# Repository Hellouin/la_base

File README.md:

# PROJET BASE RTK
## GPSE2026 - ENSICAEN
### Une base RTK permet de corriger des erreurs GPS

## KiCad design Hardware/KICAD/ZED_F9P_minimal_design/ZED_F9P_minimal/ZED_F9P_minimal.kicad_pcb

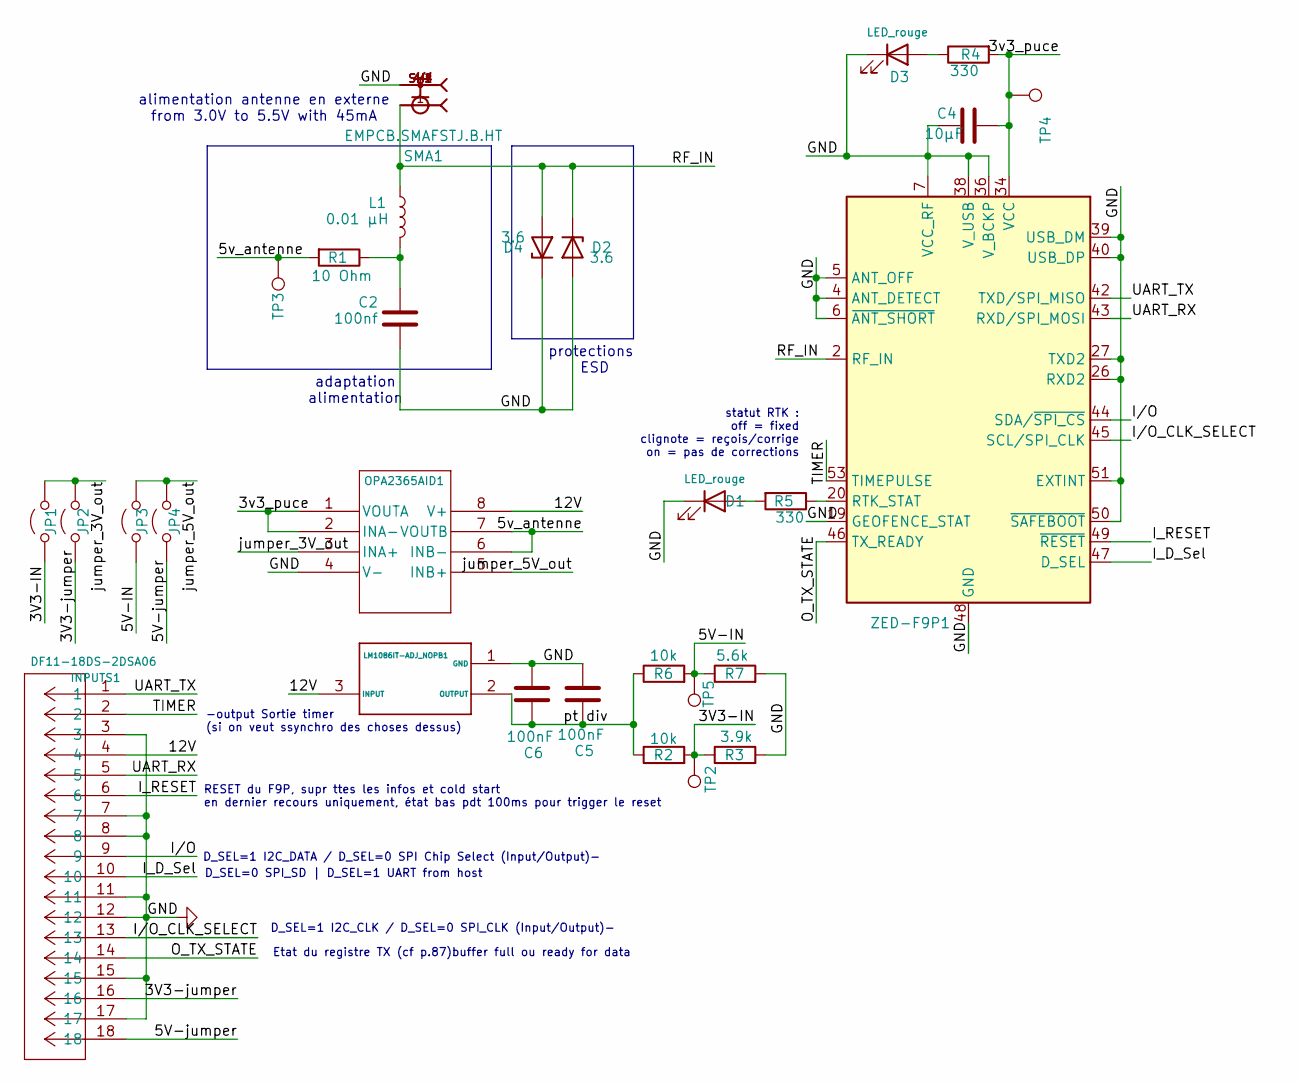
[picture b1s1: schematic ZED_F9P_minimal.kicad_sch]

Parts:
C2: 100nf; C_0805_2012Metric
C4: 10µF; C_0805_2012Metric
C5, C6: 100nF; C_0805_2012Metric
D1, D3: LED_rouge; LED_0805_2012Metric
D2, D4: 3.6; SOD323_DIO
INPUTS1: DF11-18DS-2DSA06; CON18_2X9_U_DF11_HIR
JP1, JP2, JP3, JP4: Jumper_2_Open; CON_1x02
L1: 0.01 µH; IND_786110A_WRE
LM1086IT-ADJ_NOPB1: NDE0003B
OPA2365AID1: D8
R1: 10 Ohm; RC0805N_YAG
R2, R6: 10k; YAG_R0805_YAG
R3: 3.9k; RC0805N_YAG
R4, R5: 330; RC0805N_YAG
R7: 5.6k; RC0805N_YAG
SMA1: EMPCB.SMAFSTJ.B.HT; TAOGLAS_EMPCB.SMAFSTJ.B.HT
TP2, TP3, TP4, TP5: TestPoint; CONN1_5011_KEY
ZED-F9P1: ZED-F9P; ublox_ZED

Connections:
/3V3-IN: JP1.1 (A), R2.2, R3.1, TP2.1
/3V3-jumper: INPUTS1.16, JP2.1 (A)
/3v3_puce: C4.1, OPA2365AID1.1 (VOUTA), OPA2365AID1.2 (INA-), R4.2, TP4.1, ZED-F9P1.33 (VCC), ZED-F9P1.34 (VCC)
/5V-IN: JP3.1 (A), R6.2, R7.1, TP5.1
/5V-jumper: INPUTS1.18, JP4.1 (A)
/5v_antenne: OPA2365AID1.6 (INB-), OPA2365AID1.7 (VOUTB), R1.2, TP3.1
/12V: INPUTS1.4, LM1086IT-ADJ_NOPB1.3 (INPUT), OPA2365AID1.8 (V+)
/I_D_Sel: INPUTS1.10, ZED-F9P1.47 (D_SEL)
/I_RESET: INPUTS1.6, ZED-F9P1.49 (~RESET)
/I/O: INPUTS1.9, ZED-F9P1.44 (SDA/~SPI_CS)
/I/O_CLK_SELECT: INPUTS1.13, ZED-F9P1.45 (SCL/SPI_CLK)
/O_TX_STATE: INPUTS1.14, ZED-F9P1.46 (TX_READY)
/RF_IN: D2.1 (K), D4.2 (A), L1.1, SMA1.1, ZED-F9P1.2 (RF_IN)
/TIMER: INPUTS1.2, ZED-F9P1.53 (TIMEPULSE)
/UART_RX: INPUTS1.5, ZED-F9P1.43 (RXD/SPI_MOSI)
/UART_TX: INPUTS1.1, ZED-F9P1.42 (TXD/SPI_MISO)
/jumper_3V_out: JP1.2 (B), JP2.2 (B), OPA2365AID1.3 (INA+)
/jumper_5V_out: JP3.2 (B), JP4.2 (B), OPA2365AID1.5 (INB+)
/pt div: C5.1, C6.1, LM1086IT-ADJ_NOPB1.2 (OUTPUT), R2.1, R6.1
GND: C2.2, C4.2, C5.2, C6.2, D1.1 (K), D2.2 (A), D3.1 (K), D4.1 (K), INPUTS1.3, INPUTS1.7, INPUTS1.8, INPUTS1.11, INPUTS1.12, INPUTS1.15, INPUTS1.17, LM1086IT-ADJ_NOPB1.1 (GND), OPA2365AID1.4 (V-), R3.2, R7.2, SMA1.SH1, SMA1.SH2, SMA1.SH3, SMA1.SH4, ZED-F9P1.1 (GND), ZED-F9P1.3 (GND), ZED-F9P1.4 (ANT_DETECT), ZED-F9P1.5 (ANT_OFF), ZED-F9P1.6 (~ANT_SHORT), ZED-F9P1.7 (VCC_RF), ZED-F9P1.12 (GND), ZED-F9P1.14 (GND), ZED-F9P1.19 (GEOFENCE_STAT), ZED-F9P1.26 (RXD2), ZED-F9P1.27 (TXD2), ZED-F9P1.32 (GND), ZED-F9P1.36 (V_BCKP), ZED-F9P1.37 (GND), ZED-F9P1.38 (V_USB), ZED-F9P1.39 (USB_DM), ZED-F9P1.40 (USB_DP), ZED-F9P1.41 (GND), ZED-F9P1.48 (GND), ZED-F9P1.50 (~SAFEBOOT), ZED-F9P1.51 (EXTINT), ZED-F9P1.55 (GND)
unnamed: C2.1, L1.2, R1.1
unnamed: D1.2 (A), R5.2
unnamed: D3.2 (A), R4.1
unnamed: R5.1, ZED-F9P1.20 (RTK_STAT)

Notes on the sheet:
alimentation antenne en externe from 3.0V to 5.5V with 45mA
RESET du F9P, supr ttes les infos et cold start en dernier recours uniquement, état bas pdt 100ms pour trigger le reset
D_SEL=1 I2C_DATA / D_SEL=0 SPI Chip Select (Input/Output)-
-output Sortie timer (si on veut ssynchro des choses dessus)
D_SEL=1 I2C_CLK / D_SEL=0 SPI_CLK (Input/Output)-
protections ESD
statut RTK : off = fixed clignote = reçois/corrige on = pas de corrections
Etat du registre TX (cf p.87)buffer full ou ready for data
D_SEL=0 SPI_SD | D_SEL=1 UART from host
adaptation alimentation

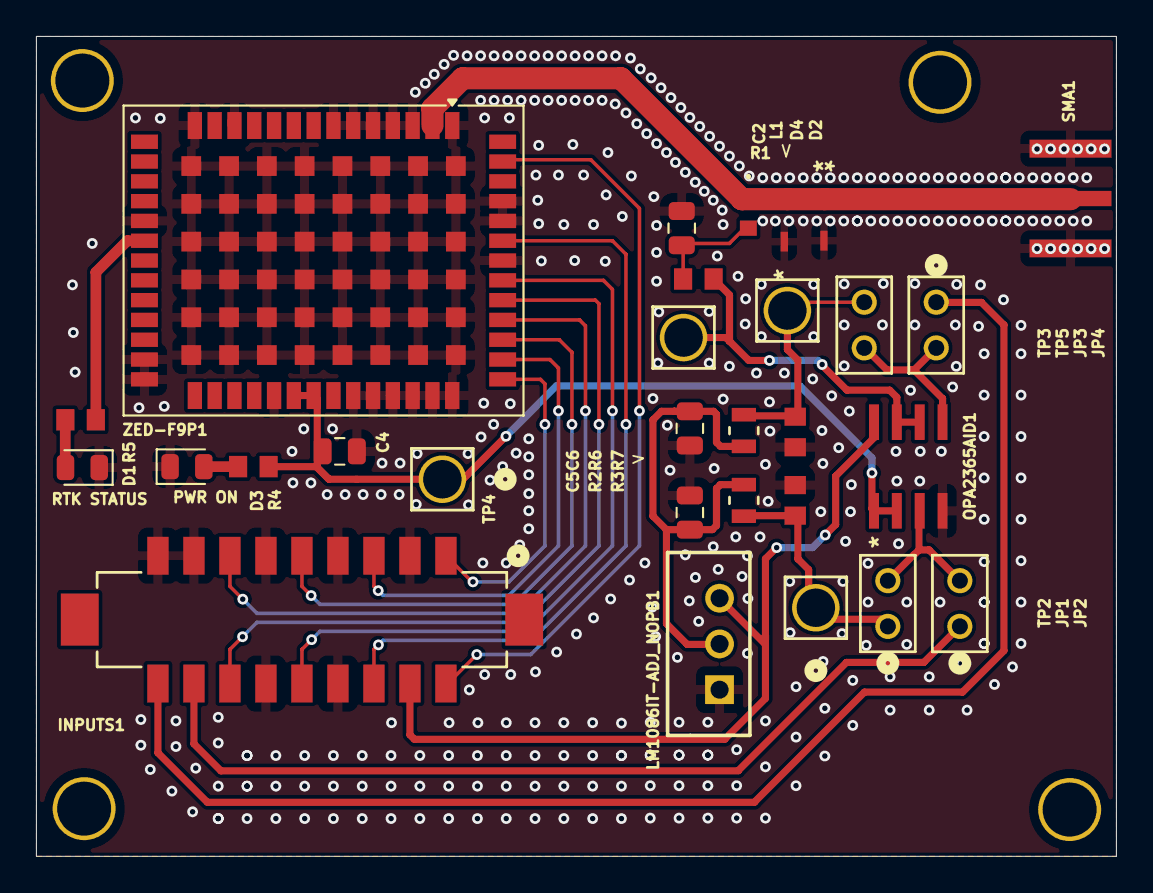
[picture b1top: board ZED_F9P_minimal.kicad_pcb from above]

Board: 2 copper layers, 60.0 x 45.5 mm, 33 parts (0 on the bottom side), 24 nets.

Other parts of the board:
REF: NPTH_test
REF#2, REF#3, REF#4: NPTH_test

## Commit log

2024-09-05 create repo folder structure
2024-09-05 miaou
2024-09-06 Create README.txt
    README
2024-09-06 README Format
2024-09-06 Create .gitignore
    Ignore useless files for Kicad project in the folder :
    KICAD/
2024-09-06 Ignore temp file Kicad
2024-09-07 ZED_F9P_miniam design
2024-09-07 ZEDF9P_min_design_WIP
2024-09-07 create code base for the firmware. it name is basjump
2024-09-07 add things to codebase
2024-09-07 add things to codebase round 2
2024-09-09 change folder organization
2024-09-25 moved ground
2024-11-05 tcp echo server typical exemple (without RTOS) + change projet name
2024-11-05 tcp echo server typical exemple (without RTOS) + change projet name + doc round 3
2024-11-05 retirer des dossiers qui n'ont rien à foutre là
2024-11-05 retirer des dossiers qui n'ont rien à foutre là2
2024-11-05 retirer des dossiers qui n'ont rien à foutre là3
2024-11-05 retirer des dossiers qui n'ont rien à foutre là4
2024-11-08 add unit test function system
2024-11-08 add unit test function system-2
2024-11-18 work on schematic and footprint
2024-11-30 commit update
2024-12-06 TODO UART modification
    Les PORTs UART DOIVENT etre déplacer sur les PIN 42 et 43 Pour utiliser UART 1 et non 2\nUART 2 a des fonctionaliser en moins
2024-12-07 Revert "Update PCB + Sync"
2024-12-07 Revert "Merge pull request #4 from Hellouin/revert-3-Hardware"
    This reverts commit f65eca79ef9561d423b3cc759dac13f79c60af08, reversing
    changes made to 40a2f59a197ca208cb9a9f6f547a003a62667144.
2024-12-07 On est presque bon je crois...
    JPP
2024-12-07 finished adding footprint started PCB layout
2024-12-07 added arguement_ublox_txt
2024-12-08 quelque modif visuel sur le shema
    quelque modif visuel sur le shema
2024-12-09 work on schematic
    besoin ajout connecteur I/O et ALIM/GND
    besoin ajout regulo de tension (en cours de choix)
    besoin footprint composant (attente feu vert)
2024-12-09 Delete Arguments_ublox
    Pas besoin
2024-12-09 fix backup
2024-12-09 Modification lisibilité
    Modification lisibilité
2025-02-15 commit avant de switch de branch
2025-02-16 http server in progress
2025-03-03 finalised first iteration of schematic
    schematic 1.0,, gonna start pcb rooting
2025-03-17 changed diode footprint
2025-04-12 Z9P PCB
    arranged placement, rooting still to do
2025-04-14 rooting pcb
    work in progerss
2025-04-15 rooting PCB
    added ground plane, rooted and shaped critical input signal for 50ohm impedance
2025-04-16 corrections
    added SMA connector and actualised pin connector footprint
2025-04-16 PCB rooting
    finalised PCB rooting
2025-04-18 files generation
    gerbers an drill generation
2025-04-22 modifications
    corrected critical mistakes on rf input
    added power on state led
    removed RF input testpoint
2025-05-01 fab files
    modifs
2025-05-01 update for eurocircuit
    waiting on aurocircuit account verification to correct pcb error
2025-05-04 manufacturing
    update and check for jlcpcb
2025-05-06 final correction
    corrected height of the pcb for JLCPCB standards
2025-05-06 update
    update
2025-05-31 final commit - rtos_dev branch
2025-05-31 final commit - rtos_dev branch 2
